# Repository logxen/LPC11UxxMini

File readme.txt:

LPC11Uxx Mini
----------------------------------------------------------------------------------

This is a basic breakout board for the NXP LPC11U24 ARM Cortex-M0 microcontroller 
with usb. It has a similar pinout and form factor to an Arduino Mini. However, it
is a bit longer to accomodate the usb and isp button.

The MCP1252 vreg accepts from 2.5V to 5.5V for running off the RAW pin when usb is 
not connected. When usb is connected the RAW pin provides access to the 'raw' 5V 
usb power. The vreg provides 120mA of 3.3V to run the mcu and some low power 
accessories connected to the VCC pin.

Features:

* program via usb msc (i.e. drag'n'drop new rom to update code)
* on board 3.3V buck/boost voltage regulator
* 22 digital gpio pins including uart, spi, i2c and 8 adc pins
* power indication led and user led (user led is connected to gpio pin D9)
* reset button and isp/user button (isp button is held at boot to enter 
        programming mode and otherwise may be used by user code)

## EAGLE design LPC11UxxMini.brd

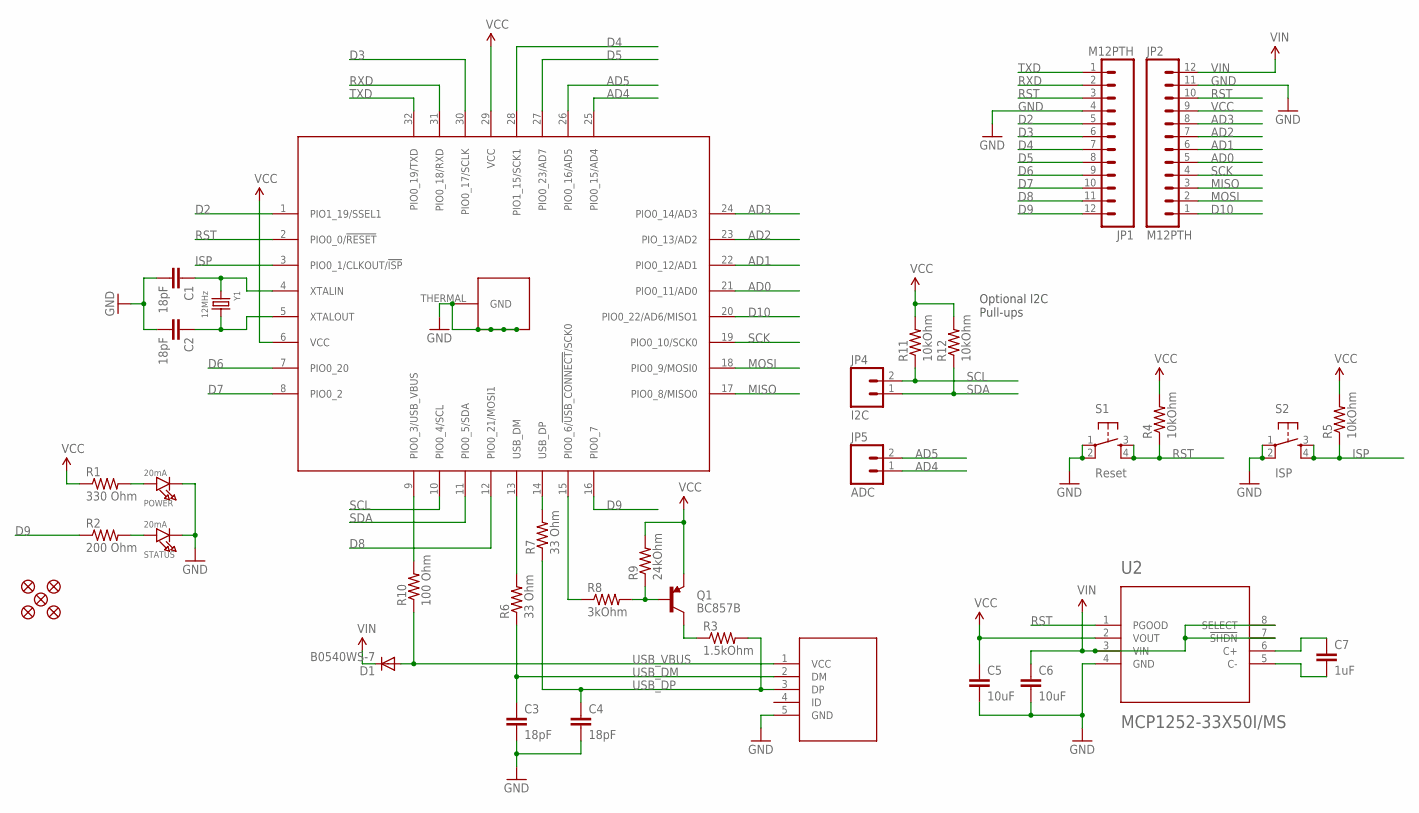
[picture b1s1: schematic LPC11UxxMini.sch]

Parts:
C1, C2, C3, C4: 18pF; 0603-CAP
C5, C6: 10uF; 1206
C7: 1uF; 0805
D1: B0540WS-7; SOD-323
JP1, JP2: M12PTH; 1X12
JP3, JP6, JP7, JP8, JP9: FIDUCIALUFIDUCIAL; MICRO-FIDUCIAL
JP4: I2C; 1X02
JP5: ADC; 1X02
POWER: 20mA; CHIPLED_0603_NOOUTLINE
Q1: BC857B; SOT23-3
R1: 330 Ohm; 0402-RES
R2: 200 Ohm; 0402-RES
R3: 1.5kOhm; 0402-RES
R4, R5, R11, R12: 10kOhm; 0402-RES
R6, R7: 33 Ohm; 0402-RES
R8: 3kOhm; 0402-RES
R9: 24kOhm; 0402-RES
R10: 100 Ohm; 0402-RES
S1: Reset; TACTILE_SWITCH_SMD
S2: ISP; TACTILE_SWITCH_SMD
STATUS: 20mA; CHIPLED_0603_NOOUTLINE
U1: LPC11Uxx; HVQFN32-5X5_3MMTHERMAL
U2: MCP1252-33X50I/MS; MSOP8_0.65MM
U$1: USB-MICROB-SMDRECEPT; USB-MICROB-RECEPT
Y1: 12MHz; CRYSTAL_2.5X2

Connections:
AD0: JP2.5, U1.21 (PIO0_11/AD0)
AD1: JP2.6, U1.22 (PIO0_12/AD1)
AD2: JP2.7, U1.23 (PIO_13/AD2)
AD3: JP2.8, U1.24 (PIO0_14/AD3)
AD4: JP5.1, U1.25 (PIO0_15/AD4)
AD5: JP5.2, U1.26 (PIO0_16/AD5)
D2: JP1.5, U1.1 (PIO1_19/SSEL1)
D3: JP1.6, U1.30 (PIO0_17/SCLK)
D4: JP1.7, U1.28 (PIO1_15/SCK1)
D5: JP1.8, U1.27 (PIO0_23/AD7)
D6: JP1.9, U1.7 (PIO0_20)
D7: JP1.10, U1.8 (PIO0_2)
D8: JP1.11, U1.12 (PIO0_21/MOSI1)
D9: JP1.12, R2.1, U1.16 (PIO0_7)
D10: JP2.1, U1.20 (PIO0_22/AD6/MISO1)
GND: C1.2, C2.2, C3.2, C4.2, C5.2, C6.2, JP1.4, JP2.11, POWER.C, S1.1, S1.2, S2.1, S2.2, STATUS.C, U1.THERMAL (GND), U1.THERMAL@1 (GND), U1.THERMAL@2 (GND), U1.THERMAL@3 (GND), U1.THERMAL@4 (GND), U2.4 (GND), U$1.5 (GND)
ISP: R5.1, S2.3, S2.4, U1.3 (PIO0_1/CLKOUT/!ISP!)
MC_USB_DM: R6.2, U1.13 (USB_DM)
MC_USB_DP: R7.2, U1.14 (USB_DP)
MC_USB_VBUS: R10.2, U1.9 (PIO0_3/USB_VBUS)
MISO: JP2.3, U1.17 (PIO0_8/MISO0)
MOSI: JP2.2, U1.18 (PIO0_9/MOSI0)
POWER_LED_RESISTOR: POWER.A, R1.2
PWRREG_C+: C7.1, U2.6 (C+)
PWRREG_C-: C7.2, U2.5 (C-)
RST: JP1.3, JP2.10, R4.1, S1.3, S1.4, U1.2 (PIO0_0/!RESET!), U2.1 (PGOOD)
RXD: JP1.2, U1.31 (PIO0_18/RXD)
SCK: JP2.4, U1.19 (PIO0_10/SCK0)
SCL: JP4.2, R11.1, U1.10 (PIO0_4/SCL)
SDA: JP4.1, R12.1, U1.11 (PIO0_5/SDA)
STATUS_LED_RESISTOR: R2.2, STATUS.A
TXD: JP1.1, U1.32 (PIO0_19/TXD)
USB_CONNECT: R8.1, U1.15 (PIO0_6/!USB_CONNECT!/SCK0)
USB_CONNECT_BASE: Q1.1 (B), R8.2, R9.1
USB_CONNECT_COLLECTOR: Q1.3 (C), R3.1
USB_DM: C3.1, R6.1, U$1.2 (DM)
USB_DP: C4.1, R3.2, R7.1, U$1.3 (DP)
USB_VBUS: D1.2 (A), R10.1, U$1.1 (VCC)
VCC: C5.1, JP2.9, Q1.2 (E), R1.1, R4.2, R5.2, R9.2, R11.2, R12.2, U1.6 (VCC), U1.29 (VCC), U2.2 (VOUT)
VIN: C6.1, D1.1 (C), JP2.12, U2.3 (VIN), U2.7 (!SHDN), U2.8 (SELECT)
XTALIN: C1.1, U1.4 (XTALIN), Y1.1
XTALOUT: C2.1, U1.5 (XTALOUT), Y1.3 (2)

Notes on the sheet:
Optional I2C Pull-ups

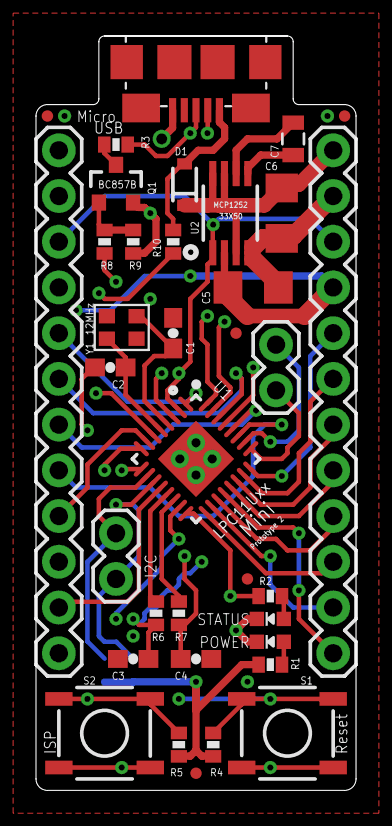
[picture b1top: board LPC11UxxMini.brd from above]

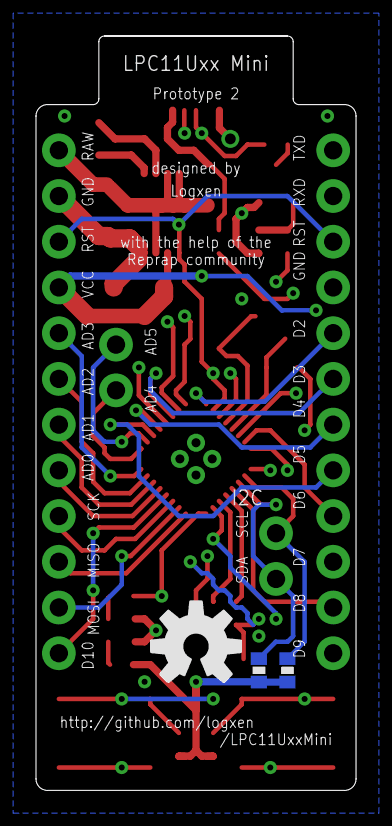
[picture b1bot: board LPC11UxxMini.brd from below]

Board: 4 copper layers, 17.8 x 41.9 mm, 39 parts (3 on the bottom side), 42 nets.

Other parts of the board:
U$4: OSHW-LOGO-M

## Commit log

2013-03-07 Initial commit (Prototype 1)
2013-03-24 Squished to true Arduino Pro Mini form factor (Prototype 2)
    also added pin_map.txt
2013-03-24 Added BoM
2013-03-24 Removed extra BoM file
2013-03-25 Added pull-down to P0_3 USB_VBUS
    leaving P0_3 floating does not seem to reliably select serial
    programming mode vs. usb programming mode, so a 10k pull-down was added
    to assert serial mode when usb power is not present.

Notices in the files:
parts and their libraries:
microbuilder: This work is placed in the public domain, and may be freely used for commercial and non-commercial work with the following conditions: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
SparkFun-Capacitors: Licensing: CC v3.0 Share-Alike You are welcome to use this library for commercial purposes.
